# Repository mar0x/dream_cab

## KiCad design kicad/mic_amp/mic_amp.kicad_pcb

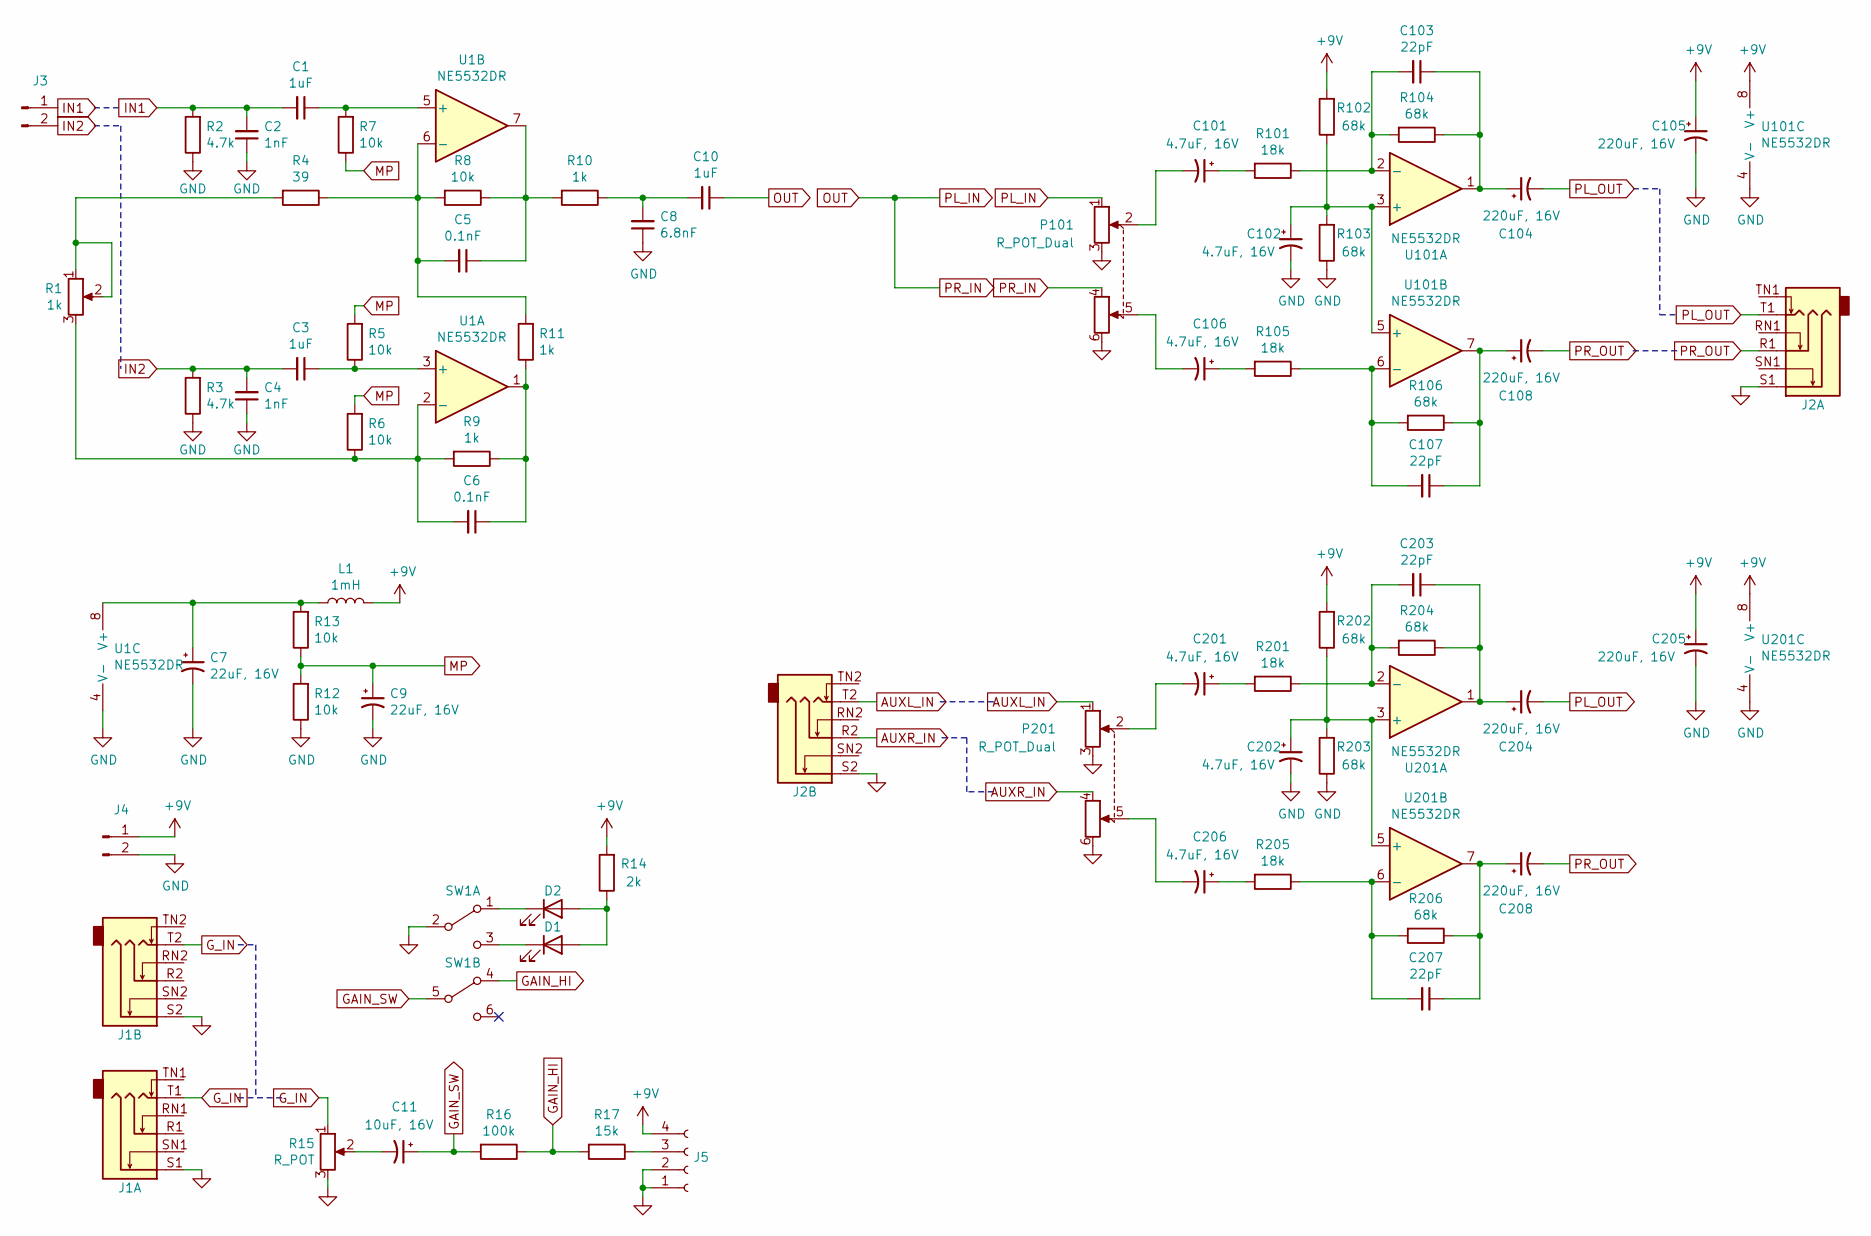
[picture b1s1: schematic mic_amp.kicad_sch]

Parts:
C1, C3, C10: 1uF; C_0805_2012Metric
C2, C4: 1nF; C_0805_2012Metric
C5, C6: 0.1nF; C_0805_2012Metric
C7, C9: 22uF, 16V; CP_Elec_5x5.4
C8: 6.8nF; C_0805_2012Metric
C11: 10uF, 16V; CP_Elec_4x5.4
C101, C102, C106, C201, C202, C206: 4.7uF, 16V; CP_Elec_4x5.4
C103, C107, C203, C207: 22pF; C_0805_2012Metric
C104, C105, C108, C204, C205, C208: 220uF, 16V; CP_Elec_6.3x7.7
D1, D2: LED; LED_D3.0mm_Horizontal_O3.81mm_Z6.0mm
J1, J2: AudioJack3_Dual_Switch; CK635-037
J3: Conn_01x02_Male; JST_PH_B2B-PH-K_1x02_P2.00mm_Vertical
J4: Conn_01x02_Male; JST_XH_B2B-XH-A_1x02_P2.50mm_Vertical
J5: Conn_01x04_Female; PinSocket_1x04_P2.54mm_Vertical
L1: 1mH; L_Radial_D7.8mm_P5.00mm_Fastron_07HCP
P101, P201: R_POT_Dual; Potentiometer_Alps_RK097_Dual_Horizontal
R1: 1k; Potentiometer_Bourns_3339P_Vertical
R2, R3: 4.7k; R_0805_2012Metric
R4: 39; R_0805_2012Metric
R5, R6, R7, R8, R12, R13: 10k; R_0805_2012Metric
R9, R10, R11: 1k; R_0805_2012Metric
R14: 2k; R_0805_2012Metric
R15: R_POT; JST_PH_B3B-PH-K_1x03_P2.00mm_Vertical
R16: 100k; R_0805_2012Metric
R17: 15k; R_0805_2012Metric
R101, R105, R201, R205: 18k; R_1206_3216Metric
R102, R103, R104, R106, R202, R203, R204, R206: 68k; R_1206_3216Metric
SW1: SW_DPDT_x2; MTS-202-C3_DPDT_Angled
U1, U101, U201: NE5532DR; SOIC-8_3.9x4.9mm_P1.27mm

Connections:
+9V: C105.1, C205.1, J4.1, J5.4, L1.2, R14.2, R102.2, R202.2, U101.8 (V+), U201.8 (V+)
AUXL_IN: J2.T2, P201.1
AUXR_IN: J2.R2, P201.4
GAIN_HI: R16.1, R17.2, SW1.4 (A)
GAIN_SW: C11.1, R16.2, SW1.5 (B)
GND: C2.1, C4.1, C7.2, C8.1, C9.2, C102.2, C105.2, C202.2, C205.2, J1.S1, J1.S2, J2.S1, J2.S2, J4.2, J5.1, J5.2, P101.3, P101.6, P201.3, P201.6, R2.1, R3.1, R12.1, R15.3, R103.1, R203.1, SW1.2 (B), U1.4 (V-), U101.4 (V-), U201.4 (V-)
G_IN: J1.T1, J1.T2, R15.1
IN1: C1.2, C2.2, J3.1, R2.2
IN2: C3.2, C4.2, J3.2, R3.2
MP: C9.1, R5.2, R6.2, R7.1, R12.2, R13.1
unnamed: C1.1, R7.2, U1.5 (+)
unnamed: C3.1, R5.1, U1.3 (+)
unnamed: C5.1, R8.1, R10.2, U1.7
unnamed: C5.2, R4.1, R8.2, R11.2, U1.6 (-)
unnamed: C6.1, R9.1, R11.1, U1.1
unnamed: C6.2, R1.3, R6.1, R9.2, U1.2 (-)
unnamed: C8.2, C10.2, R10.1
unnamed: C11.2, R15.2
unnamed: C101.2, P101.2
unnamed: C103.1, C104.1, R104.1, U101.1
unnamed: C103.2, R101.1, R104.2, U101.2 (-)
unnamed: C106.2, P101.5
unnamed: C107.1, C108.1, R106.1, U101.7
unnamed: C107.2, R105.1, R106.2, U101.6 (-)
unnamed: C201.2, P201.2
unnamed: C203.1, C204.1, R204.1, U201.1
unnamed: C203.2, R201.1, R204.2, U201.2 (-)
unnamed: C206.2, P201.5
unnamed: C207.1, C208.1, R206.1, U201.7
unnamed: C207.2, R205.1, R206.2, U201.6 (-)
unnamed: D1.1 (K), SW1.3 (C)
unnamed: D1.2 (A), D2.2 (A), R14.1
unnamed: D2.1 (K), SW1.1 (A)
unnamed: J5.3, R17.1
unnamed: C7.1, L1.1, R13.2, U1.8 (V+)
unnamed: R1.1, R1.2, R4.2
unnamed: C101.1, R101.2
unnamed: C102.1, R102.1, R103.2, U101.3 (+), U101.5 (+)
unnamed: C106.1, R105.2
unnamed: C201.1, R201.2
unnamed: C202.1, R202.1, R203.2, U201.3 (+), U201.5 (+)
unnamed: C206.1, R205.2
OUT: C10.1, P101.1, P101.4
PL_OUT: C104.2, C204.2, J2.T1
PR_OUT: C108.2, C208.2, J2.R1

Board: 2 copper layers, 70 parts (0 on the bottom side), 45 nets, no tracks yet.

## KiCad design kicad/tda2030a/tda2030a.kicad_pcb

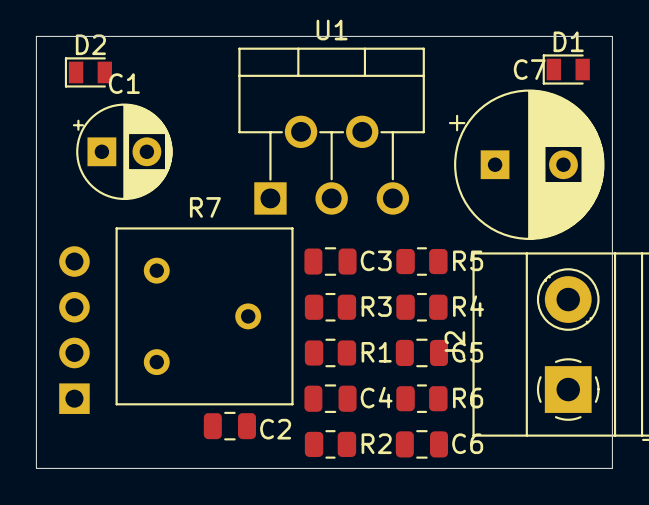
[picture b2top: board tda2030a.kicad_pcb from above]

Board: 2 copper layers, 32.0 x 24.0 mm, 19 parts (1 on the bottom side), 11 nets, no tracks yet.

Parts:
C1: 100uF; CP_Radial_D5.0mm_P2.50mm
C2, C5: 2.2uF; C_0805_2012Metric
C3: 1uF; C_0805_2012Metric
C4: 22uF; C_0805_2012Metric
C6: 220nF; C_0805_2012Metric
C7: 2000uF; CP_Radial_D8.0mm_P3.80mm
D1, D2: 1N4001; D_MicroMELF
J1: Conn_01x04_Male; PinHeader_1x04_P2.54mm_Vertical
J2: Conn_01x02_Female; TerminalBlock_Phoenix_MKDS-1,5-2_1x02_P5.00mm_Horizontal
R1, R2, R3: 100k; R_0805_2012Metric
R4: 4.7k; R_0805_2012Metric
R5: 150k; R_0805_2012Metric
R6: 1R; R_0805_2012Metric
R7: 10k; Potentiometer_Bourns_3386F_Vertical
U1: TDA2030; TO-220-5_P3.4x3.7mm_StaggerOdd_Lead3.8mm_Vertical

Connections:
GND: C1.2, C2.2, C4.2, C5.2, C6.2, D1.2, J1.1, J1.2, J2.2, R3.1, R7.3, U1.3
unnamed: C3.1, R7.2
unnamed: C3.2, R2.2, U1.1
unnamed: C4.1, R1.1, R2.1, R3.2
unnamed: C5.1, R4.1
unnamed: C6.1, R6.1
unnamed: C7.1, D1.1, D2.2, R5.1, R6.2, U1.4
unnamed: C7.2, J2.1
unnamed: J1.3, R7.1
unnamed: R4.2, R5.2, U1.2
VCC: C1.1, C2.1, D2.1, J1.4, R1.2, U1.5

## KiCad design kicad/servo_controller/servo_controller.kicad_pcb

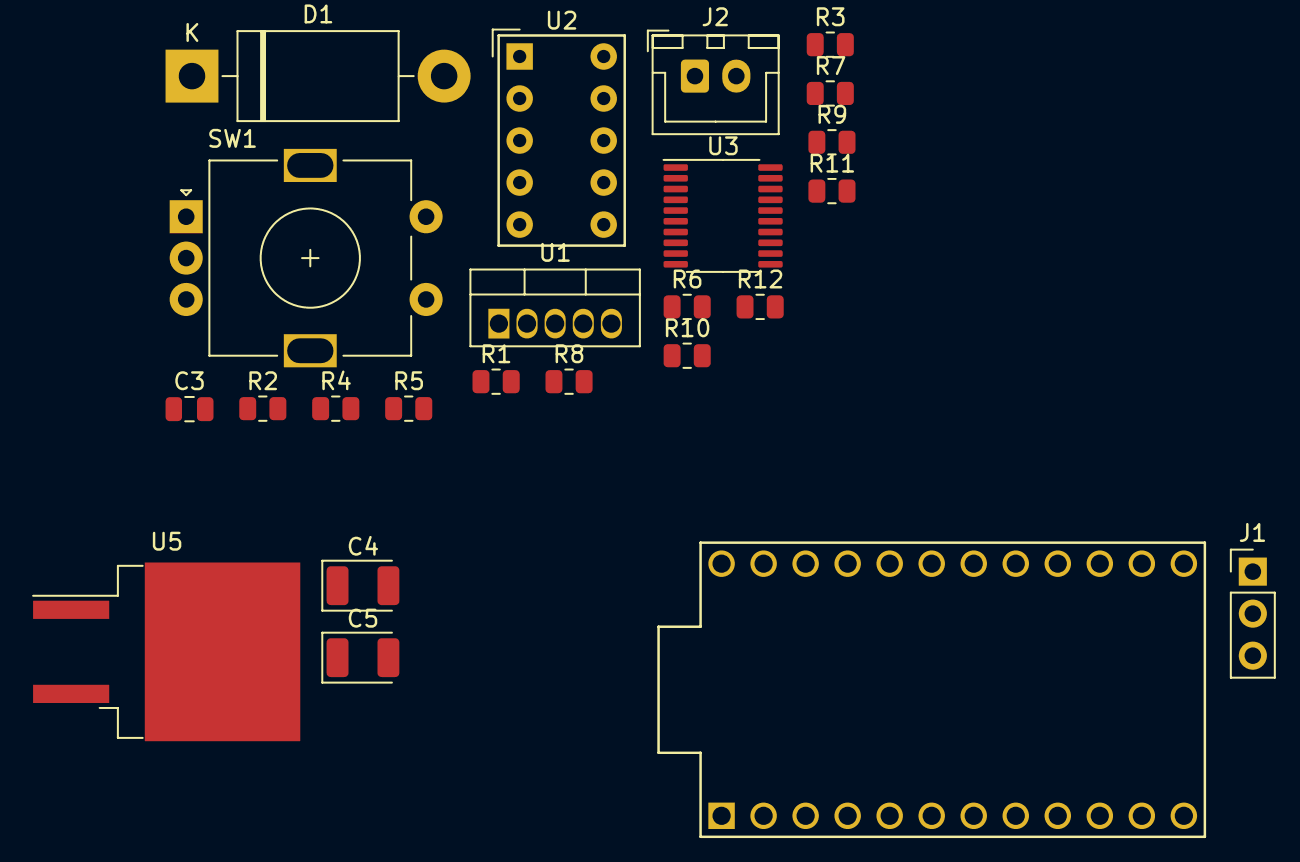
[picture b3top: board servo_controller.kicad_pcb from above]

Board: 2 copper layers, 24 parts (0 on the bottom side), 32 nets, no tracks yet.

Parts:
C3: 0.1uF; C_0805_2012Metric
C4, C5: 10uF; CP_EIA-3528-12_Kemet-T
D1: 1N5822; D_DO-201AD_P15.24mm_Horizontal
J1: Conn_01x03_Male; PinHeader_1x03_P2.54mm_Vertical
J2: Conn_01x02_Male; JST_XH_B2B-XH-A_1x02_P2.50mm_Vertical
R1, R2, R3, R6, R7, R8, R9, R10: 470; R_0805_2012Metric
R4, R5, R11, R12: 39k; R_0805_2012Metric
SW1: Rotary_Encoder_Switch; RotaryEncoder_Alps_EC11E-Switch_Vertical_H20mm
U1: LM2576HVT-5; TO-220-5_Vertical
U2: HDSP-A153; HDSP-A151
U3: 74HCT541; TSSOP-20_4.4x6.5mm_P0.65mm
U4: ProMicro
U5: NCP1117-5.0_SOT223; TO-263-2

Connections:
+5V: C3.2, C5.1, J1.2, R4.1, R5.1, R11.2, R12.2, U1.4, U3.20, U4.21, U5.2
+9V: C4.1, J2.1, U1.1, U5.3
BTN: R5.2, SW1.S1
ENCA: R4.2, SW1.A, U4.11
ENCB: R11.1, SW1.B, U4.12
GND: C3.1, C4.2, C5.2, D1.2, J1.3, J2.2, SW1.C, SW1.S2, U1.3, U1.5, U2.1, U2.6, U3.10, U4.3, U4.4, U4.23, U5.1
LED1: U3.2, U4.20
LED2: U3.3, U4.19
LED3: U3.4, U4.18
LED4: U3.5, U4.17
LED5: U3.6, U4.16
LED6: U3.7, U4.15
LED7: U3.8, U4.14
LED8: U3.9, U4.13
unnamed: D1.1, U1.2
unnamed: R1.1, U3.18
unnamed: R1.2, U2.10
unnamed: R2.1, U3.17
unnamed: R2.2, U2.9
unnamed: R3.1, U3.16
unnamed: R3.2, U2.8
unnamed: R6.1, U3.15
unnamed: R6.2, U2.5
unnamed: R7.1, U3.14
unnamed: R7.2, U2.4
unnamed: R8.1, U3.13
unnamed: R8.2, U2.2
unnamed: R9.1, U3.12
unnamed: R9.2, U2.3
unnamed: R10.1, U3.11
unnamed: R10.2, U2.7
OEN: R12.1, U3.1, U3.19

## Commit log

2022-11-30 Join kicad libs
2022-11-30 Migrating to KiCad6
2026-02-23 One more box project
2026-02-23 Add ignore patterns
2026-02-23 Migrating to KiCad 9
